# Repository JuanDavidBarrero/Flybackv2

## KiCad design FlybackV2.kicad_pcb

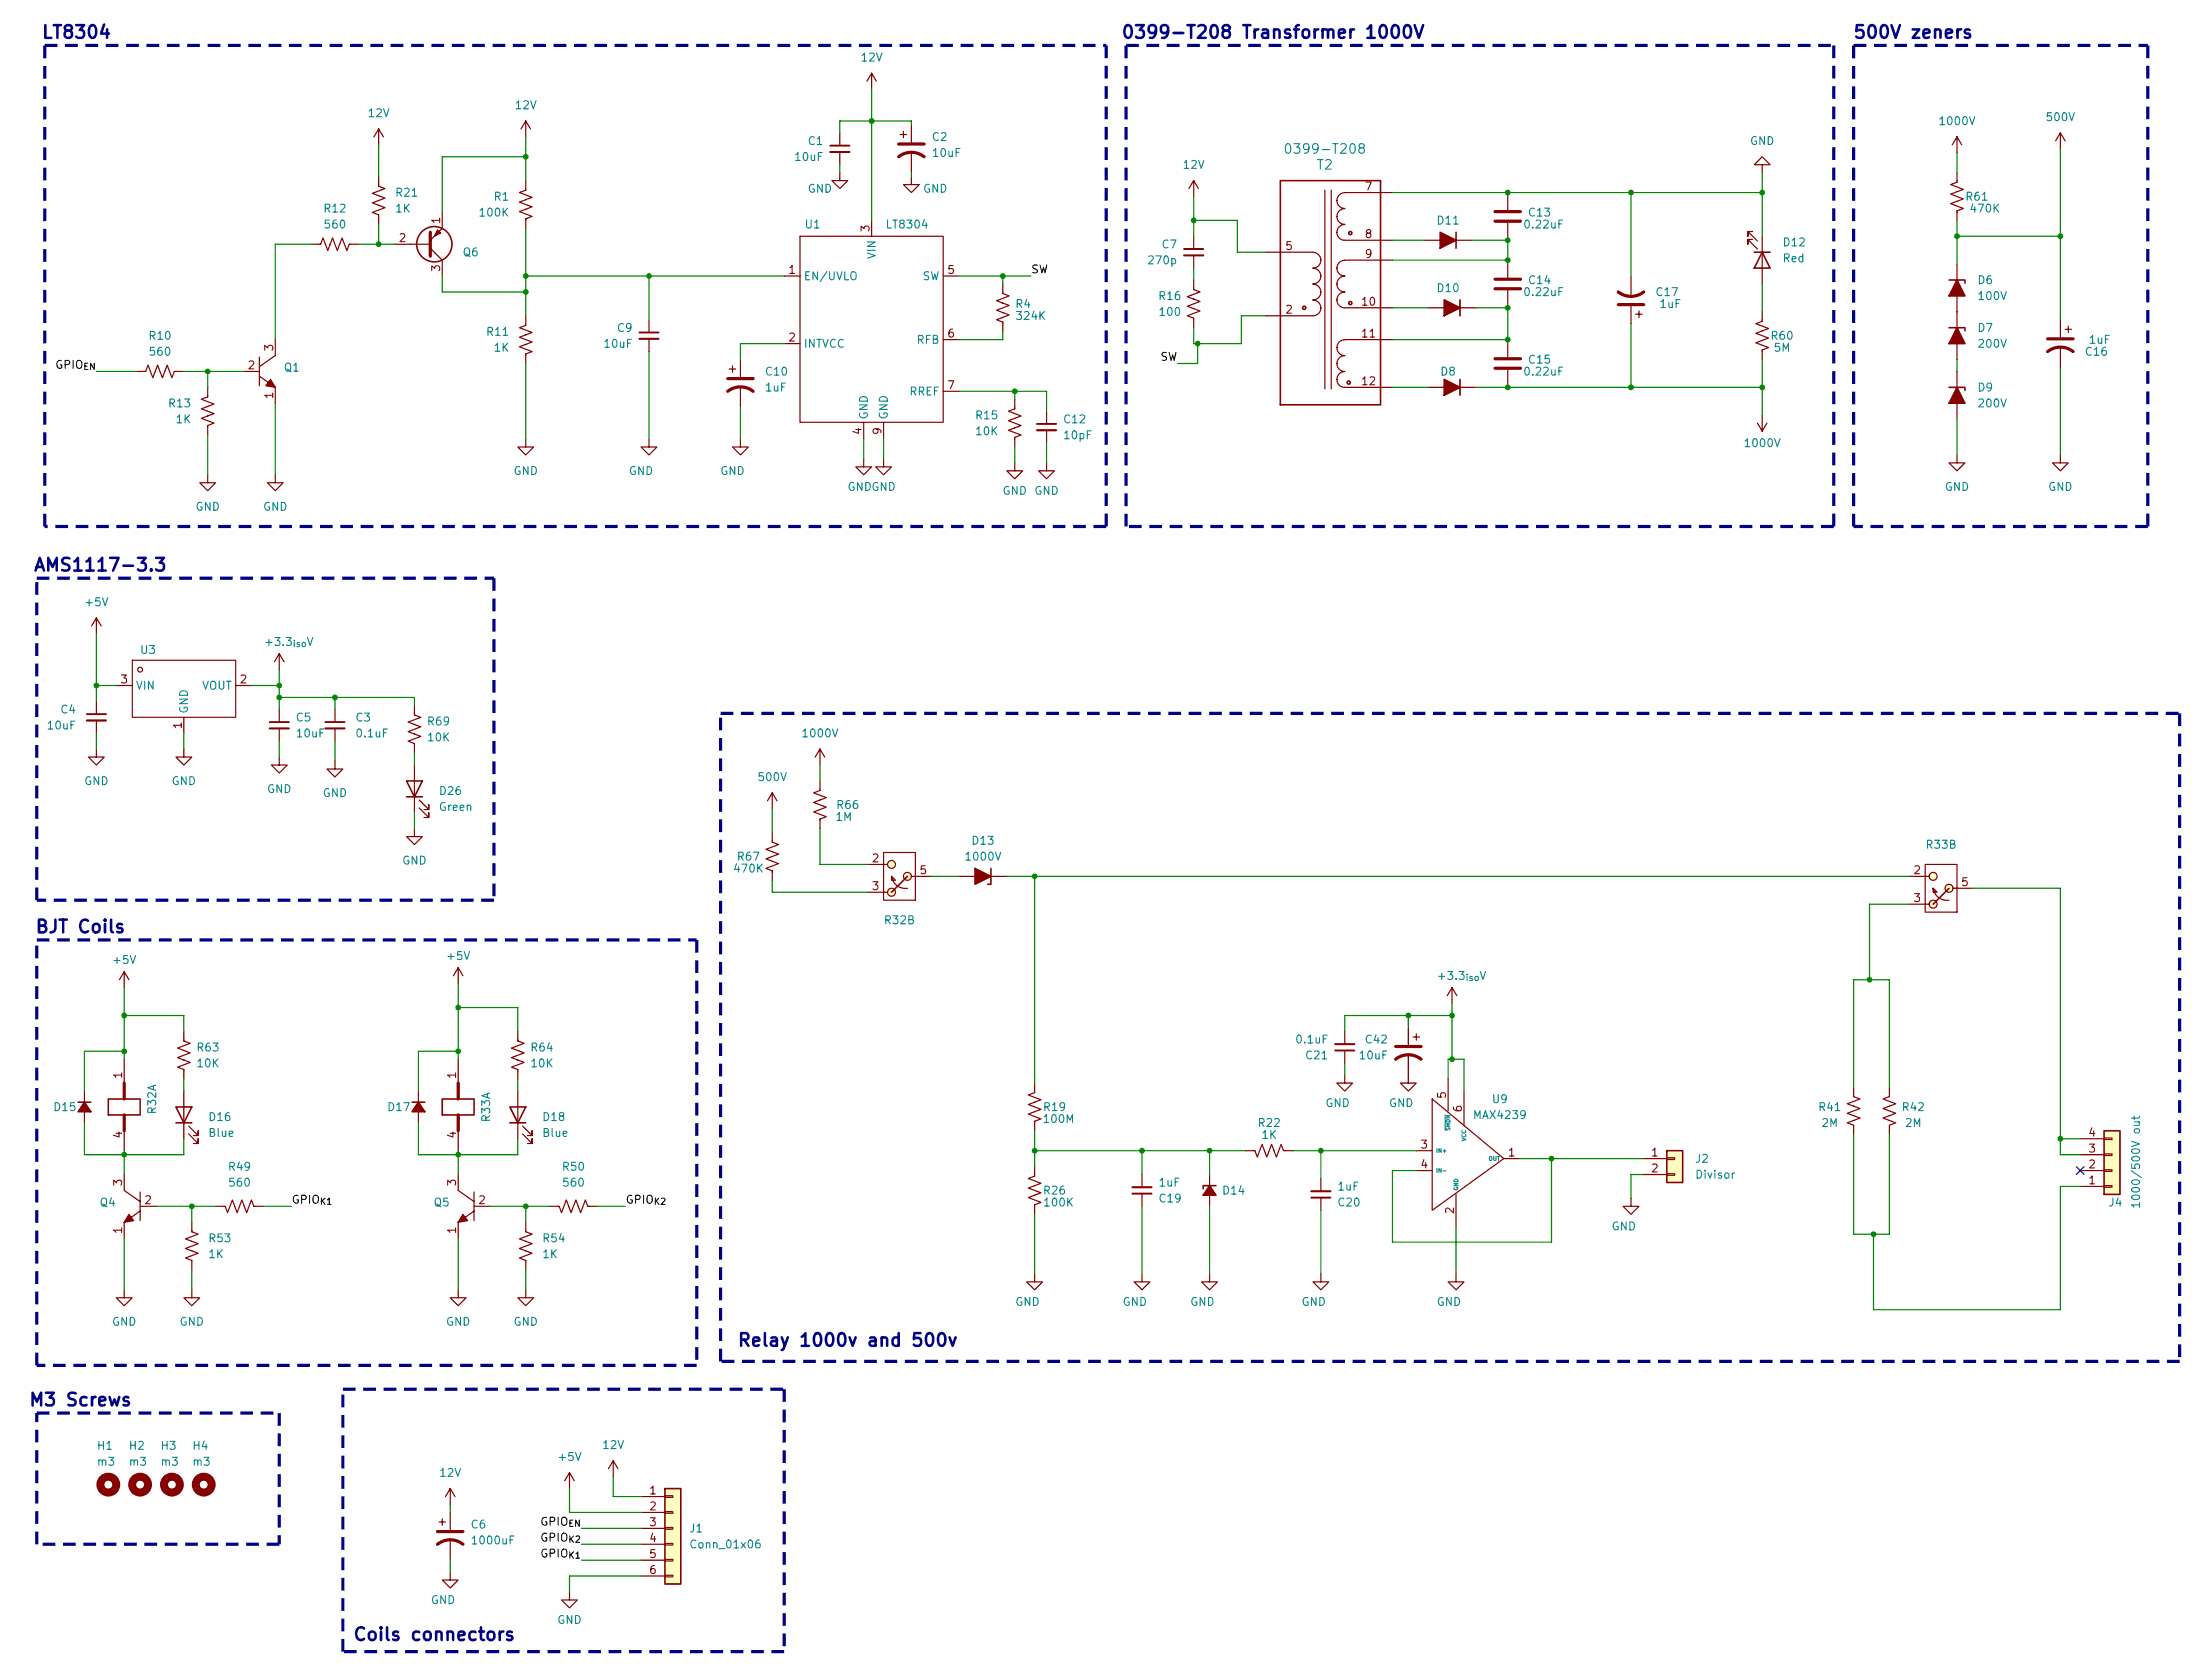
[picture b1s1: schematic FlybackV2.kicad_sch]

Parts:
C1, C2, C4, C5, C9, C42: 10uF; C_0805_2012Metric; LCSC Part C237493
C3, C21: 0.1uF; C_0805_2012Metric; LCSC Part C28233
C6: 1000uF; CP_Radial_D13.0mm_P5.00mm
C7: 270p; C_0805_2012Metric; LCSC Part C113828
C10, C19, C20: 1uF; C_0805_2012Metric; LCSC Part C28323
C12: 10pF; C_0805_2012Metric; LCSC Part C157608
C13, C14, C15: 0.22uF; C_2220_5750Metric; LCSC Part C153037
C16, C17: 1uF; CP_Axial_L18.0mm_D8.0mm_P25.00mm_Horizontal
D6: 100V; D_A-405_P10.16mm_Horizontal
D7, D9: 200V; D_A-405_P10.16mm_Horizontal
D8, D10, D11: D_Filled; D_SOD-123
D12: Red; LED_0805_2012Metric; LCSC Part C84256
D13: 1000V; D_A-405_P5.08mm_Vertical_KathodeUp
D14: D_Zener_Small_Filled; D_A-405_P10.16mm_Horizontal
D15, D17: D_Small_Filled; D_A-405_P10.16mm_Horizontal
D16, D18: Blue; LED_0805_2012Metric; LCSC Part C2293
D26: Green; LED_0805_2012Metric; LCSC Part C2297
H1, H2, H3, H4: m3; MountingHole_3.2mm_M3
J1: Conn_01x06; PinHeader_1x06_P2.54mm_Vertical
J2: Divisor; TerminalBlock_Phoenix_MKDS-1,5-2-5.08_1x02_P5.08mm_Horizont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
J4: 1000/500V out; TerminalBlock_Phoenix_MKDS-1,5-4-5.08_1x04_P5.08mm_Horizont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
Q1, Q4, Q5: TO-92-3_L4.9-W3.7-P2.54-L; LCSC Part C2874602
Q6: 2N3906; TO-92_Inline; LCSC Part C9809
R1: 100K; R_1206_3216Metric; LCSC Part C17900
R4: 324K; R_1206_3216Metric; LCSC Part C5266167
R10, R12, R49, R50: 560; R_1206_3216Metric; LCSC Part C17994
R11, R13, R21, R22, R53, R54: 1K; R_1206_3216Metric; LCSC Part C4410
R15, R63, R64, R69: 10K; R_1206_3216Metric; LCSC Part C17902
R16: 100; R_1206_3216Metric; LCSC Part C862084
R19: 100M; R_Axial_DIN0207_L6.3mm_D2.5mm_P15.24mm_Horizontal
R26: 100K; R_Axial_DIN0207_L6.3mm_D2.5mm_P15.24mm_Horizontal
R32, R33: RELAY-TH_SRD-XXVDC-XL-C
R41, R42: 2M; R_Axial_DIN0207_L6.3mm_D2.5mm_P15.24mm_Horizontal
R60: 5M; R_Axial_DIN0207_L6.3mm_D2.5mm_P15.24mm_Horizontal
R61, R67: 470K; R_Axial_DIN0207_L6.3mm_D2.5mm_P15.24mm_Horizontal
R66: 1M; R_Axial_DIN0207_L6.3mm_D2.5mm_P15.24mm_Horizontal
T2: 0399-T208; SO12_21X21-3_SUM; DigiKey Part Number 308-2599-2-ND
U1: LT8304; SOIC-8_L4.9-W3.9-P1.27-LS6.0-BL-EP3.3; LCSC Part C673691
U3: SOT-223-3_L6.5-W3.4-P2.30-LS7.0-BR; LCSC Part C6186
U9: MAX4239; SOT-23-6_L2.9-W1.6-P0.95-LS2.9-BL; LCSC Part C479740

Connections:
12V: C1.1, C2.1, C6.1, C7.1, J1.1, Q6.1 (E), R1.1, R21.1, T2.5, U1.3 (VIN)
500V: C16.1, D6.1 (K), R61.1, R67.2
1000V: C15.1, C17.1, D8.1 (K), R60.1, R61.2, R66.2
+3.3_{iso}V: C3.1, C5.1, C21.2, C42.1, R69.2, U3.2 (VOUT), U3.4 (VOUT), U9.5 (~SHDN), U9.6 (VCC)
+5V: C4.1, D15.1 (K), D17.1 (K), J1.2, R32.1, R33.1, R63.2, R64.2, U3.3 (VIN)
/GPIO_{EN}: J1.3, R10.2
/GPIO_{K1}: J1.5, R49.2
/GPIO_{K2}: J1.4, R50.2
/SW: R4.1, R16.1, T2.2, U1.5 (SW)
GND: C1.2, C2.2, C3.2, C4.2, C5.2, C6.2, C9.2, C10.2, C12.2, C13.2, C16.2, C17.2, C19.1, C20.1, C21.1, C42.2, D9.2 (A), D12.1 (K), D14.2 (A), D26.1 (K), J1.6, J2.2, Q1.1, Q4.1, Q5.1, R11.2, R13.2, R15.2, R26.1, R53.2, R54.2, T2.7, U1.4 (GND), U1.9 (GND), U3.1 (GND), U9.2 (GND)
unnamed: C7.2, R16.2
unnamed: D6.2 (A), D7.1 (K)
unnamed: D7.2 (A), D9.1 (K)
unnamed: D8.2 (A), T2.12
unnamed: D10.2 (A), T2.10
unnamed: C14.1, C15.2, D10.1 (K), T2.11
unnamed: D11.2 (A), T2.8
unnamed: C13.1, C14.2, D11.1 (K), T2.9
unnamed: D12.2 (A), R60.2
unnamed: D13.2 (A), R32.5
unnamed: D13.1 (K), R19.2, R33.2
unnamed: C19.2, D14.1 (K), R19.1, R22.2, R26.2
unnamed: D15.2 (A), D16.1 (K), Q4.3, R32.4
unnamed: D16.2 (A), R63.1
unnamed: D17.2 (A), D18.1 (K), Q5.3, R33.4
unnamed: D18.2 (A), R64.1
unnamed: D26.2 (A), R69.1
unnamed: J2.1, U9.1 (OUT), U9.4 (IN-)
unnamed: J4.1, R41.1, R42.1
unnamed: J4.3, J4.4, R33.5
unnamed: Q1.2, R10.1, R13.1
unnamed: Q1.3, R12.2
unnamed: Q4.2, R49.1, R53.1
unnamed: Q5.2, R50.1, R54.1
unnamed: Q6.2 (B), R12.1, R21.2
unnamed: C9.1, Q6.3 (C), R1.2, R11.1, U1.1 (EN/UVLO)
unnamed: R32.2, R66.1
unnamed: R32.3, R67.1
unnamed: R33.3, R41.2, R42.2
unnamed: C10.1, U1.2 (INTVCC)
unnamed: R4.2, U1.6 (RFB)
unnamed: C12.1, R15.1, U1.7 (RREF)
unnamed: C20.2, R22.1, U9.3 (IN+)

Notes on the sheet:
Coils connectors
0399-T208 Transformer 1000V
500V zeners
AMS1117-3.3
M3 Screws
BJT Coils
Relay 1000v and 500v
LT8304

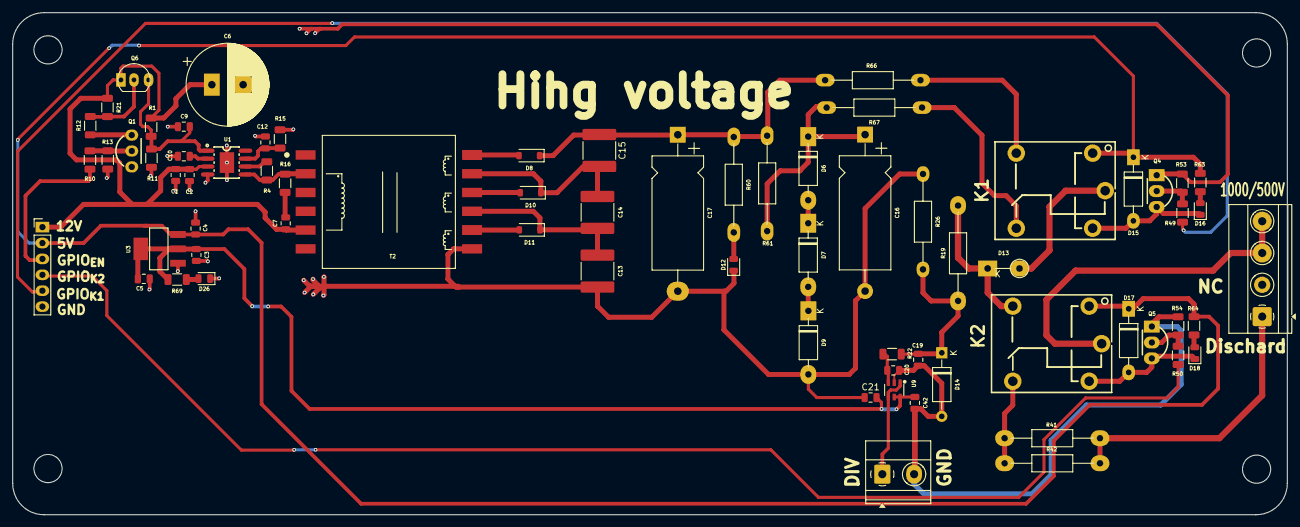
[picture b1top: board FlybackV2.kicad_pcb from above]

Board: 2 copper layers, 203.7 x 80.2 mm, 75 parts (0 on the bottom side), 43 nets.

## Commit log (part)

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2025-06-30 the pcb is routed
2025-07-01 v2 now with pnp transistor
2025-07-08 finish v2 version
2025-08-07 init: new version
2025-08-08 update: init the track of the pcb
2025-08-08 finish the route, in revision
2025-08-11 flyback finish route
2025-08-16 now has a C for the 12V source
2025-08-17 update: it versin goes to production
2025-08-21 update: order in the schematic
2025-09-20 finish
2025-11-30 uptade: jlcs part number
2026-03-30 minor
